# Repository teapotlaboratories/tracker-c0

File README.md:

# Tracker C0: Low-power Cellular GPS Tracker

Tracker C0 is a small, low-cost tracker board from Teapot Laboratories. It reports its position over LTE Cat-1 and is
meant to run for **at least a year on one battery**. To get there it spends almost all of its time in deep sleep,
wakes up when the accelerometer feels movement, takes a GNSS fix, sends a report over the cellular network, and goes
back to sleep with the modem and GNSS fully powered off.

> Formerly BWLC1A; the old GitHub URL redirects here.

| | |
|---|---|
| **Revision** | Rev 5 in progress on `main` (adds fiducials). Rev 4 (tag `rev4`) is ordered and not yet built or measured. |
| **Controller** | Espressif ESP32-S3-MINI-1-N4R2 (U4): Wi-Fi, Bluetooth LE, USB, deep sleep with RTC wake |
| **Cellular** | SIMCom A7670G-LABE (U1), LTE Cat-1, nano-SIM (J1) |
| **GNSS** | Quectel L96-M33 (U3), GPS / GLONASS / Galileo / BeiDou, built-in antenna, battery-backed hot starts |
| **Motion wake** | ST LSM6DSO 6-axis IMU (U11), INT1 to an RTC-capable ESP32 pin |
| **Battery** | Single-cell LiPo on a JST-PH 2-pin connector (J4), MAX17048 fuel gauge (U10) |
| **Charging** | USB-C (J3), MCP73831 linear charger (U8), 500 mA |
| **LTE antenna** | TE 2108784-1 PCB antenna (E1), or a u.FL connector (J6/J7) selected by resistors |
| **Expansion** | Qwiic / STEMMA QT I²C connector (J5), Tag-Connect TC2050 JTAG pads (J2), reset and boot buttons (SW1, SW2) |
| **Board** | 83.75 × 50.0 mm, 4 layers, 1.6 mm, 50 Ω coplanar antenna feed, all parts on the top side |

## Gallery

| Top | Bottom |
|---|---|
|  |  |
|  |  |

## Architecture

```mermaid
flowchart LR
    USB["USB-C<br/>J3"] -->|VBUS| CHG["MCP73831<br/>charger U8"]
    USB -->|"USB D+/D−"| MCU
    CHG --> BATT(("+BATT"))
    CELL["LiPo cell<br/>J4"] -->|"Q3 reverse<br/>protection"| BATT

    BATT --> LDO["RT9080 3.3 V<br/>always on"]
    LDO -->|+3V3| MCU["ESP32-S3<br/>U4"]
    LDO -->|+3V3| IMU["LSM6DSO<br/>IMU"]
    BATT --> FG["MAX17048<br/>fuel gauge"]
    BATT -->|"Q7 switch<br/>CELL_EN"| MODEM["A7670G<br/>LTE modem"]
    BATT -->|"TPS7A03 LDO<br/>GNSS_EN"| GNSS["L96-M33<br/>GNSS"]
    BATT -->|V_BCKP| GNSS

    IMU -->|"INT1 → GPIO14<br/>(wake)"| MCU
    FG -->|"ALERT → GPIO18"| MCU
    MCU <-->|"I²C (+ Qwiic J5)"| IMU
    MCU <-->|I²C| FG
    MCU <-->|"UART 3.3 V"| SHIFT["TXB0102<br/>level shifter"]
    SHIFT <-->|"UART 1.8 V"| MODEM
    MCU -->|"PWRKEY / RESET<br/>open-drain FETs"| MODEM
    MODEM -->|"STATUS → inverter"| MCU
    MCU <-->|UART| GNSS
    MODEM --- SIM["nano-SIM"]
    MODEM --- ANT["LTE antenna E1<br/>or u.FL J6/J7"]
```

### Power

Everything runs from the single-cell battery rail **+BATT**. While the tracker sleeps, only the 3.3 V regulator and
what it feeds (ESP32, IMU, the idle TXB0102 B side), the fuel gauge and the GNSS backup domain are powered.

| Rail | Source | Feeds | Switched by |
|---|---|---|---|
| +BATT | LiPo through Q3 (PMV32UP, reverse protection); charged by U8 from USB | everything below | always on |
| +3V3 | U6 RT9080-33 LDO | ESP32-S3, LSM6DSO, TXB0102 B side, Qwiic J5 | always on |
| CELL_BATT | +BATT through Q7 (PMV32UP P-FET), driven by Q8 (2N7002) | A7670G VBAT (soft start ~15 ms) | CELL_EN, GPIO13 |
| GNSS_3V3 | U7 TPS7A0333 LDO | L96-M33 VCC | GNSS_EN, GPIO4 |
| V_BCKP | +BATT directly | L96-M33 backup (keeps ephemeris for hot starts) | always on |
| VDD_1V8 | A7670G output | TXB0102 A side | on while the modem is on |

The modem draws up to about 2 A in bursts, so it takes its supply straight from the battery through a P-FET switch
rather than through a regulator.

### Operating cycle

```mermaid
stateDiagram-v2
    [*] --> DeepSleep
    DeepSleep --> Fix: IMU motion interrupt (GPIO14)<br/>or RTC timer
    Fix --> Report: GNSS_EN high, wait for a fix<br/>(hot start from V_BCKP)
    Report --> Shutdown: CELL_EN high, PWRKEY pulse,<br/>STATUS low = modem up, send report
    Shutdown --> DeepSleep: AT+CPOF, then CELL_EN low<br/>GNSS_EN low
```

### Estimated sleep budget

Datasheet typical values, **not measured yet**. Details and sources are in the
[Rev 4 change report](docs/worklog/2026-11-19-rev4-changes.html).

| In deep sleep | Current |
|---|---|
| ESP32-S3, RTC on for wake | 8 µA |
| LSM6DSO, low-power wake-up mode | 4.4 to 9.5 µA |
| L96-M33 backup domain | 7 µA |
| MAX17048, hibernate | 3 to 5 µA |
| RT9080 quiescent | 2 µA |
| TXB0102, charger, switched-off regulators, ESD | ≤ 4 µA |
| **Total** | **about 27 to 40 µA, about 240 to 350 mAh per year** |

With an assumed 1.5 mAh per wake-up (about 20 s GNSS fix plus 30 s LTE report), four wake-ups a day fit a 3 to 4 Ah
LiPo for one year. Measure sleep and event current on the first boards before choosing the cell.

## ESP32-S3 pin map

| GPIO | Net | Use |
|---|---|---|
| GPIO0 | BOOT_MODE0 | Boot strap, BOOT button SW2 |
| GPIO1 | GNSS_RESET | L96 reset, **drive open-drain only** (no pull-up) |
| GPIO4 | GNSS_EN | GNSS LDO enable |
| GPIO5 | GNSS_FO | L96 force-on |
| GPIO6 | GNSS_EXTINT | L96 external interrupt |
| GPIO7 / GPIO8 | GNSS_RXD / GNSS_TXD | GNSS UART |
| GPIO9 | CELL_PWRKEY | Modem PWRKEY through Q4, active high |
| GPIO10 / GPIO11 | CELL_TXD / CELL_RXD | Modem UART through the TXB0102 |
| GPIO12 | CELL_RESET | Modem RESET through Q5, active high |
| GPIO13 | CELL_EN | Modem battery switch Q7 |
| GPIO14 | IMU_INT | LSM6DSO INT1, deep-sleep wake source |
| GPIO17 | CELL_STATUS_N | Modem STATUS through the Q6 inverter, **low = modem on** |
| GPIO18 | FG_INT | MAX17048 ALERT |
| GPIO19 / GPIO20 | USB_D− / USB_D+ | Native USB on the USB-C connector |
| GPIO21 | GNSS_STAT | L96 status |
| GPIO36 / GPIO37 | SCL / SDA | I²C: IMU, fuel gauge, Qwiic J5 |
| GPIO39 to GPIO42 | JTAG_TCK / TDO / TDI / TMS | Tag-Connect J2 |
| GPIO47 / GPIO48 | LEDs | D6 / D5 |
| EN | CHIP_EN | Reset button SW1, Tag-Connect J2 |

### Firmware notes

- PWRKEY and RESET are pulled up to VBAT inside the modem. They are driven only through the Q4 and Q5 open-drain
  N-FETs, which are active high. Never assert both at the same time (A7670 hardware design guide).
- Before switching the modem off with CELL_EN, send `AT+CPOF`. Wait at least 5 s before switching it on again.
- GNSS_RESET has no pull-up: drive GPIO1 open-drain only.
- The modem UART is 1.8 V on the modem side. The TXB0102 translates it and goes high-impedance while the modem's
  1.8 V rail is off, so nothing back-powers the modem.

## Schematic

The KiCad 10 project is in [`hardware/kicad/`](hardware/kicad): the root sheet `tracker-c0.kicad_sch` plus eight
sub-sheets (Power, Battery, USB and Charger, Main Controller, Cellular, GNSS, Sensors, Antenna), the board
`tracker-c0.kicad_pcb`, and project libraries in `library/`.

## Manufacturing

Production files are in [`hardware/kicad/production/`](hardware/kicad/production):

| File | Contents |
|---|---|
| `TeapotlabsTrackerC0_Gerber.zip` | Gerbers, PTH/NPTH drill, IPC-D-356 netlist, PCBWay BOM and positions |
| `TeapotlabsTrackerC0_BOM.csv` | Bill of materials: 53 lines, 112 parts, with LCSC, Mouser or Digi-Key part numbers |
| `TeapotlabsTrackerC0_CPL.csv` | Pick-and-place positions (top side only) |
| `TeapotlabsTrackerC0_ManufacturingInfo.txt` | Board spec, stack-up and impedance notes for the fab |
| `TeapotlabsTrackerC0_InteractiveBOM.html` | Interactive BOM for hand assembly and inspection (open in a browser) |

Board spec: 4 layers, 1.6 mm, S1000H TG150, 5/5 mil, 0.3 mm minimum hole, tented vias, red solder mask with white
silkscreen. The LTE antenna feed is a 50 Ω coplanar waveguide on L1 (0.33 mm trace, 0.2 mm gap, referenced to L2),
so order with impedance control. Copper stays 0.3 mm from the board edge. Use a 0.12 mm stencil: U1 (A7670G) carries
SIMCom's recommended stencil openings, which need 0.12 to 0.15 mm.

Rebuild and check the production files with KiCad 10 installed:

```
hardware/tools/fab/export_production.sh          # BOM, CPL, Gerber zip, interactive BOM
python3 hardware/tools/fab/check_production.py   # board, BOM, CPL and PCBWay files must agree (PASS/FAIL)
```

The production check for PCBWay (BOM and CPL verification, board-edge and stencil fixes, part swaps) is in
[`docs/worklog/2026-11-19-pcbway-readiness.html`](docs/worklog/2026-11-19-pcbway-readiness.html).

## What changed in Rev 5 (in progress)

- **Fiducials:** three global fiducials on the top side (FID1-FID3: 1 mm copper in a 2 mm mask opening) for
  pick-and-place alignment. They are board-only, so the BOM and CPL are unchanged.
- **Board colour:** the stack-up mask colour is set to red, so KiCad's 3D view matches the boards as ordered.

The Rev 4 files as ordered from PCBWay are tagged `rev4`.

## What changed in Rev 4

- **Modem UART translator:** the 4-channel TXB0104 became a 2-channel TXB0102. Modem RESET now has its own open-drain
  driver (Q5) on GPIO12.
- **Modem STATUS:** the 1.8 V STATUS output is read through a FET inverter (Q6), so GPIO17 sees a clean 3.3 V level.
- **Modem power:** the SY8089 buck is gone. The modem runs straight from the battery through a P-FET switch with a
  soft start.
- **GNSS:** the reset pull-up that back-fed current in sleep is removed. The GNSS backup supply is wired straight to
  the battery, so every fix is a hot start; the backup switch and jumper are gone.
- **Assembly:** the battery connector moved to the top, so the board is single-sided. The corner is cut away for the
  battery cable.
- **Schematic readability** and a refreshed set of production files.

The full report with before/after schematic, PCB and 3D views is
[`docs/worklog/2026-11-19-rev4-changes.html`](docs/worklog/2026-11-19-rev4-changes.html). Download or clone the
repository and open it in a browser; GitHub shows HTML files as source.

## Repository layout

```
hardware/
  kicad/          KiCad 10 project, libraries, 3D models
    production/   Gerbers, BOM, CPL, manufacturing notes, interactive BOM
  tools/fab/      Production export and pre-order check
  tools/ibom/     Interactive BOM generator
docs/
  images/         README images and report images (Git LFS)
  worklog/        Design change reports
```

Images under `docs/images/` and the 3D models are stored with [Git LFS](https://git-lfs.com). Install it before
cloning to get the files instead of pointer stubs.

## License

[MIT](LICENSE)

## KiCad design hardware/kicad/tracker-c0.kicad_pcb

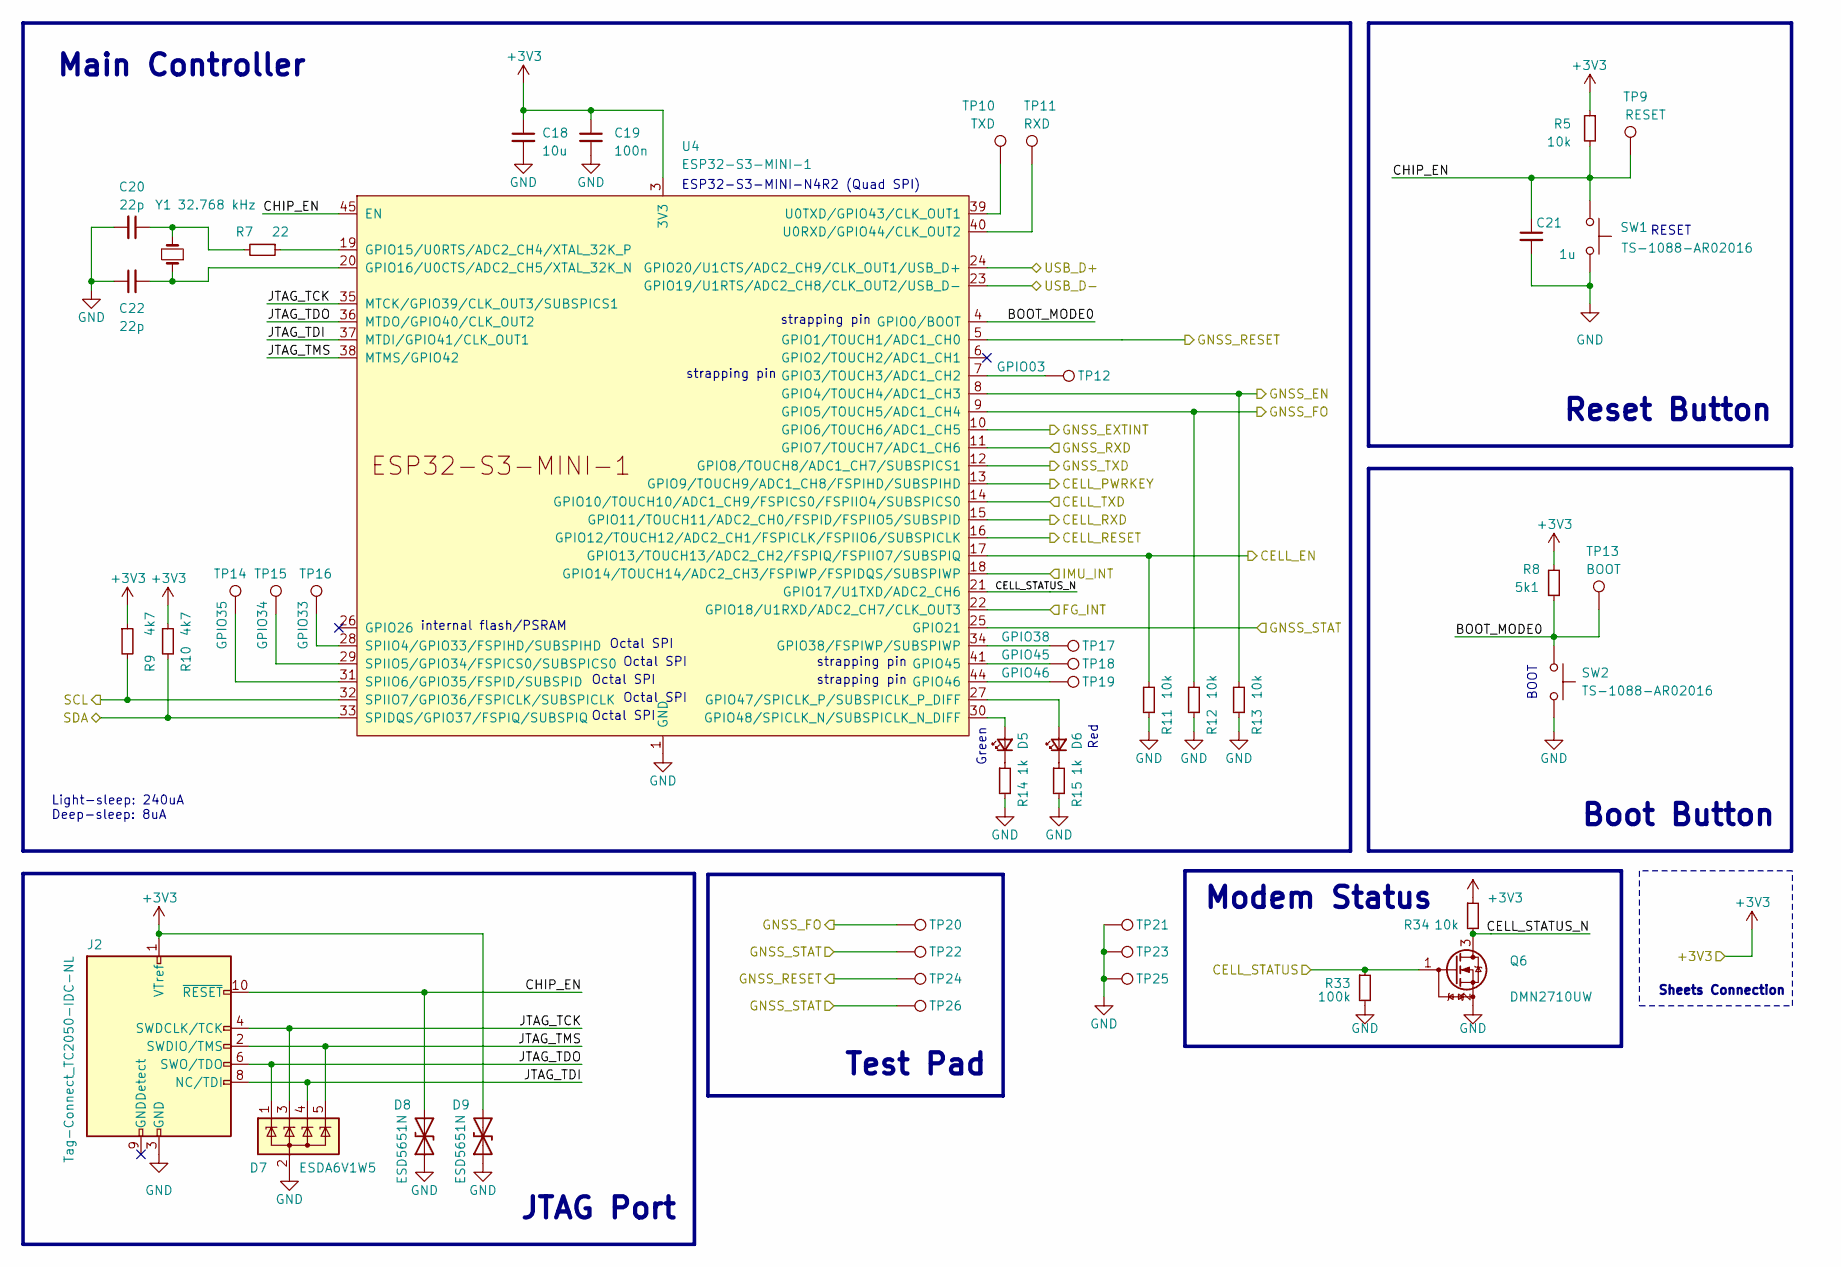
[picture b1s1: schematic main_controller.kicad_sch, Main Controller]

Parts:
C18: 10u; C_0603_1608Metric; Manufacturer Part Number CL10A106KP8NNNC
C19: 100n; C_0402_1005Metric; Manufacturer Part Number CL05B104KO5NNNC
C20, C22: 22p; C_0402_1005Metric; Manufacturer Part Number 0402CG220J500NT
C21: 1u; C_0402_1005Metric; Manufacturer Part Number CL05A105KA5NQNC
D5: LTST-C191KGKT; LED_0603_1608Metric; Manufacturer Part Number LTST-C191KGKT
D6: LTST-C191KRKT; LED_0603_1608Metric; Manufacturer Part Number LTST-C191KRKT
D7: ESDA6V1W5; SOT-353_SC-70-5; Manufacturer Part Number ESDA6V1W5
D8, D9: ESD5651N; D_SOD-882; Manufacturer Part Number ESD5651N
J2: Tag-Connect_TC2050-IDC-NL; Tag-Connect_TC2050-IDC-NL_2x05_P1.27mm_Vertical
Q6: DMN2710UW; SOT-323_SC-70; Manufacturer Part Number DMN2710UW-7
R5, R11, R12, R13, R34: 10k; R_0402_1005Metric; Manufacturer Part Number FRC0402F1002TS
R7: 22; R_0402_1005Metric; Manufacturer Part Number RC0402FR-0722RL
R8: 5k1; R_0402_1005Metric; Manufacturer Part Number 0402WGF5101TCE
R9, R10: 4k7; R_0402_1005Metric; Manufacturer Part Number 0402WGF4701TCE
R14, R15: 1k; R_0402_1005Metric; Manufacturer Part Number 0402WGF1001TCE
R33: 100k; R_0402_1005Metric; Manufacturer Part Number 0402WGF1003TCE
SW1, SW2: TS-1088-AR02016; SW-SMD_L3.9-W3.0-P4.45; Manufacturer Part Number TS-1088-AR02016
TP9: RESET; TestPoint_Pad_D1.0mm
TP10: TXD; TestPoint_Pad_D1.0mm
TP11: RXD; TestPoint_Pad_D1.0mm
TP12: GPIO03; TestPoint_Pad_D1.0mm
TP13: BOOT; TestPoint_Pad_D1.0mm
TP14: GPIO35; TestPoint_Pad_D1.0mm
TP15: GPIO34; TestPoint_Pad_D1.0mm
TP16: GPIO33; TestPoint_Pad_D1.0mm
TP17: GPIO38; TestPoint_Pad_D1.0mm
TP18: GPIO45; TestPoint_Pad_D1.0mm
TP19: GPIO46; TestPoint_Pad_D1.0mm
TP20, TP21, TP22, TP23, TP24, TP25, TP26: TestPoint_Pad_D1.0mm
U4: ESP32-S3-MINI-1; Manufacturer Part Number ESP32-S3-MINI-1-N4R2
Y1: 32.768 kHz; Crystal_SMD_3215-2Pin_3.2x1.5mm; Manufacturer Part Number Q13FC1350000400

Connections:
+3V3: C18.1, C19.1, D9.2 (A2), J2.1 (VTref), R5.1, R8.2, R9.1, R10.1, R34.1, U4.3 (3V3); also elsewhere on the board
/Cellular/CELL_PWRKEY: U4.13 (GPIO9/TOUCH9/ADC1_CH8/FSPIHD/SUBSPIHD); also elsewhere on the board
/Cellular/CELL_RESET: U4.16 (GPIO12/TOUCH12/ADC2_CH1/FSPICLK/FSPIIO6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); also elsewhere on the board
/Cellular/CELL_RXD: U4.15 (GPIO11/TOUCH11/ADC2_CH0/FSPID/FSPIIO5/S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); also elsewhere on the board
/Cellular/CELL_STATUS: Q6.1 (G), R33.1; also elsewhere on the board
/Cellular/CELL_TXD: U4.14 (GPIO10/TOUCH10/ADC1_CH9/FSPICS0/FSPIIO4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); also elsewhere on the board
/GNSS/GNSS_EXTINT: U4.10 (GPIO6/TOUCH6/ADC1_CH5); also elsewhere on the board
/GNSS/GNSS_FO: R12.2, TP20.1, U4.9 (GPIO5/TOUCH5/ADC1_CH4); also elsewhere on the board
/GNSS/GNSS_RESET: TP24.1, U4.5 (GPIO1/TOUCH1/ADC1_CH0); also elsewhere on the board
/GNSS/GNSS_RXD: U4.11 (GPIO7/TOUCH7/ADC1_CH6); also elsewhere on the board
/GNSS/GNSS_STAT: TP22.1, TP26.1, U4.25 (GPIO21); also elsewhere on the board
/GNSS/GNSS_TXD: U4.12 (GPIO8/TOUCH8/ADC1_CH7/SUBSPICS1); also elsewhere on the board
/Main Controller/BOOT_MODE0: R8.1, SW2.1, TP13.1, U4.4 (GPIO0/BOOT)
/Main Controller/CELL_EN: R11.2, U4.17 (GPIO13/TOUCH13/ADC2_CH2/FSPIQ/FSPIIO7/S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); also elsewhere on the board
/Main Controller/CELL_STATUS_N: Q6.3 (D), R34.2, U4.21 (GPIO17/U1TXD/ADC2_CH6)
/Main Controller/CHIP_EN: C21.1, D8.2 (A2), J2.10 (~RESET), R5.2, SW1.2, TP9.1, U4.45 (EN)
/Main Controller/FG_INT: U4.22 (GPIO18/U1RXD/ADC2_CH7/CLK_OUT3); also elsewhere on the board
/Main Controller/GNSS_EN: R13.2, U4.8 (GPIO4/TOUCH4/ADC1_CH3); also elsewhere on the board
/Main Controller/IMU_INT: U4.18 (GPIO14/TOUCH14/ADC2_CH3/FSPIWP/FSPIDQS/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); also elsewhere on the board
/Main Controller/JTAG_TCK: D7.3 (K), J2.4 (SWDCLK/TCK), U4.35 (MTCK/GPIO39/CLK_OUT3/SUBSPICS1)
/Main Controller/JTAG_TDI: D7.4 (K), J2.8 (NC/TDI), U4.37 (MTDI/GPIO41/CLK_OUT1)
/Main Controller/JTAG_TDO: D7.1 (K), J2.6 (SWO/TDO), U4.36 (MTDO/GPIO40/CLK_OUT2)
/Main Controller/JTAG_TMS: D7.5 (K), J2.2 (SWDIO/TMS), U4.38 (MTMS/GPIO42)
/Main Controller/SCL: R9.2, U4.32 (SPIIO7/GPIO36/FSPICLK/SUBSPICLK); also elsewhere on the board
/Main Controller/SDA: R10.2, U4.33 (SPIDQS/GPIO37/FSPIQ/SUBSPIQ); also elsewhere on the board
/Main Controller/USB_D+: U4.24 (GPIO20/U1CTS/ADC2_CH9/CLK_OUT1/USB_D+); also elsewhere on the board
/Main Controller/USB_D-: U4.23 (GPIO19/U1RTS/ADC2_CH8/CLK_OUT2/USB_D-); also elsewhere on the board
GND: C18.2, C19.2, C20.2, C21.2, C22.1, D7.2 (A), D8.1 (A1), D9.1 (A1), J2.3 (GND), J2.5 (GND), Q6.2 (S), R11.1, R12.1, R13.1, R14.2, R15.2, R33.2, SW1.1, SW2.2, TP21.1, TP23.1, TP25.1, U4.1 (GND), U4.2 (GND), U4.42 (GND), U4.43 (GND), U4.46 (GND), U4.47 (GND), U4.48 (GND), U4.49 (GND), U4.50 (GND), U4.51 (GND), U4.52 (GND), U4.53 (GND), U4.54 (GND), U4.55 (GND), U4.56 (GND), U4.57 (GND), U4.58 (GND), U4.59 (GND), U4.60 (GND), U4.61 (GND), U4.62 (GND), U4.63 (GND), U4.64 (GND), U4.65 (GND); also elsewhere on the board
unnamed: C20.1, R7.2, Y1.2
unnamed: D5.2 (A), U4.30 (GPIO48/SPICLK_N/SUBSPICLK_N_DIFF)
unnamed: D5.1 (K), R14.1
unnamed: D6.2 (A), U4.27 (GPIO47/SPICLK_P/SUBSPICLK_P_DIFF)
unnamed: D6.1 (K), R15.1
unnamed: TP12.1, U4.7 (GPIO3/TOUCH3/ADC1_CH2)
unnamed: R7.1, U4.19 (GPIO15/U0RTS/ADC2_CH4/XTAL_32K_P)
unnamed: C22.2, U4.20 (GPIO16/U0CTS/ADC2_CH5/XTAL_32K_N), Y1.1
unnamed: TP17.1, U4.34 (GPIO38/FSPIWP/SUBSPIWP)
unnamed: TP18.1, U4.41 (GPIO45)
unnamed: TP19.1, U4.44 (GPIO46)
unnamed: TP16.1, U4.28 (SPIIO4/GPIO33/FSPIHD/SUBSPIHD)
unnamed: TP15.1, U4.29 (SPIIO5/GPIO34/FSPICS0/SUBSPICS0)
unnamed: TP14.1, U4.31 (SPIIO6/GPIO35/FSPID/SUBSPID)
unnamed: TP11.1, U4.40 (U0RXD/GPIO44/CLK_OUT2)
unnamed: TP10.1, U4.39 (U0TXD/GPIO43/CLK_OUT1)

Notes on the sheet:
ESP32-S3-MINI-N4R2 (Quad SPI)
Red
Test Pad
Reset Button
strapping pin
Octal SPI
Main Controller
JTAG Port
Green
Boot Button
RESET
Sheets Connection
internal flash/PSRAM
BOOT
Light-sleep: 240uA Deep-sleep: 8uA
Modem Status

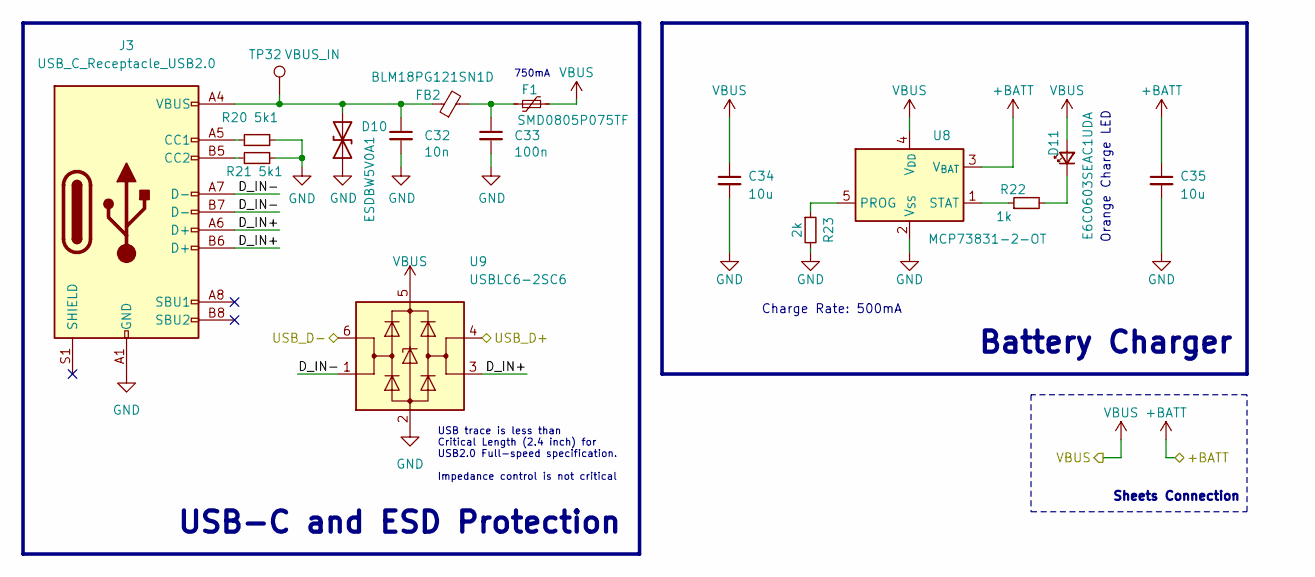
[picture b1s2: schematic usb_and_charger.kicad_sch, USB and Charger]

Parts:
C32: 10n; C_0402_1005Metric; Manufacturer Part Number CL05B103KB5NNNC
C33: 100n; C_0402_1005Metric; Manufacturer Part Number CL05B104KO5NNNC
C34, C35: 10u; C_0603_1608Metric; Manufacturer Part Number CL10A106KP8NNNC
D10: ESDBW5V0A1; D_SOD-882; Manufacturer Part Number ESDBW5V0A1
D11: E6C0603SEAC1UDA; LED_0603_1608Metric; Manufacturer Part Number E6C0603SEAC1UDA
F1: SMD0805P075TF; Fuse_0805_2012Metric; Manufacturer Part Number SMD0805P075TF
FB2: BLM18PG121SN1D; L_0603_1608Metric; Manufacturer Part Number BLM18PG121SN1D
J3: USB_C_Receptacle_USB2.0; USB_C_Receptacle_HRO_TYPE-C-31-M-12; Manufacturer Part Number TYPE-C-31-M-12
R20, R21: 5k1; R_0402_1005Metric; Manufacturer Part Number 0402WGF5101TCE
R22: 1k; R_0402_1005Metric; Manufacturer Part Number 0402WGF1001TCE
R23: 2k; R_0402_1005Metric; Manufacturer Part Number 0402WGF2001TCE
TP32: VBUS_IN; TestPoint_Pad_D1.0mm
U8: MCP73831-2-OT; SOT-23-5; Manufacturer Part Number MCP73831T-2ATI/OT
U9: USBLC6-2SC6; SOT-23-6; Manufacturer Part Number USBLC6-2SC6

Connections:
+BATT: C35.1, U8.3 (V_{BAT}); also elsewhere on the board
/Main Controller/USB_D+: U9.4 (I/O2); also elsewhere on the board
/Main Controller/USB_D-: U9.6 (I/O1); also elsewhere on the board
/USB and Charger/D_IN+: J3.A6 (D+), J3.B6 (D+), U9.3 (I/O2)
/USB and Charger/D_IN-: J3.A7 (D-), J3.B7 (D-), U9.1 (I/O1)
GND: C32.2, C33.2, C34.2, C35.2, D10.1 (A1), J3.A1 (GND), J3.A12 (GND), J3.B1 (GND), J3.B12 (GND), R20.2, R21.2, R23.2, U8.2 (V_{SS}), U9.2 (GND); also elsewhere on the board
unnamed: C33.1, F1.1, FB2.2
unnamed: C32.1, D10.2 (A2), FB2.1, J3.A4 (VBUS), J3.A9 (VBUS), J3.B4 (VBUS), J3.B9 (VBUS), TP32.1
unnamed: D11.1 (K), R22.2
unnamed: J3.A5 (CC1), R20.1
unnamed: J3.B5 (CC2), R21.1
unnamed: R23.1, U8.5 (PROG)
unnamed: R22.1, U8.1 (STAT)
VBUS: C34.1, D11.2 (A), F1.2, U8.4 (V_{DD}), U9.5 (VBUS)

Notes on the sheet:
Orange Charge LED
Battery Charger
USB trace is less than Critical Length (2.4 inch) for USB2.0 Full-speed specification. Impedance control is not critical
Sheets Connection
750mA
Charge Rate: 500mA
USB-C and ESD Protection

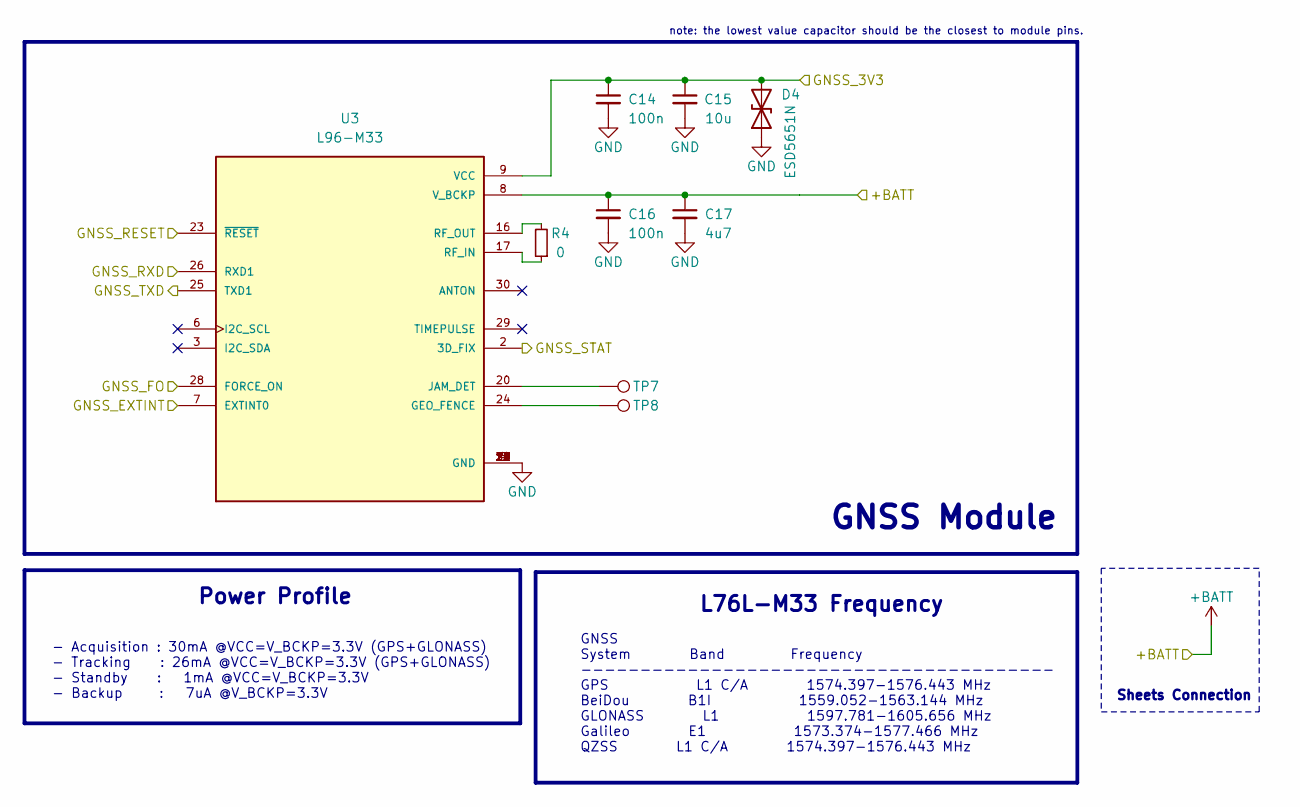
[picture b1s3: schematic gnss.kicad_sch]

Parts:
C14, C16: 100n; C_0402_1005Metric; Manufacturer Part Number CL05B104KO5NNNC
C15: 10u; C_0603_1608Metric; Manufacturer Part Number CL10A106KP8NNNC
C17: 4u7; C_0603_1608Metric; Manufacturer Part Number CL10A475KO8NNNC
D4: ESD5651N; D_SOD-882; Manufacturer Part Number ESD5651N
R4: 0; R_0402_1005Metric; Manufacturer Part Number 0402WGF0000TCE
TP7, TP8: GPIO46; TestPoint_Pad_D1.0mm
U3: L96-M33; Manufacturer Part Number L96-M33

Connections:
+BATT: C16.1, C17.1, U3.8 (V_BCKP); also elsewhere on the board
/GNSS/GNSS_EXTINT: U3.7 (EXTINT0); also elsewhere on the board
/GNSS/GNSS_FO: U3.28 (FORCE_ON); also elsewhere on the board
/GNSS/GNSS_RESET: U3.23 (~RESET); also elsewhere on the board
/GNSS/GNSS_RXD: U3.26 (RXD1); also elsewhere on the board
/GNSS/GNSS_STAT: U3.2 (3D_FIX); also elsewhere on the board
/GNSS/GNSS_TXD: U3.25 (TXD1); also elsewhere on the board
/GNSS_3V3: C14.1, C15.1, D4.2 (A2), U3.9 (VCC); also elsewhere on the board
GND: C14.2, C15.2, C16.2, C17.2, D4.1 (A1), U3.4 (GND), U3.5 (GND), U3.10 (GND), U3.11 (GND), U3.12 (GND), U3.13 (GND), U3.14 (GND), U3.15 (GND), U3.18 (GND), U3.19 (GND), U3.21 (GND), U3.22 (GND), U3.27 (GND), U3.31 (GND); also elsewhere on the board
unnamed: TP8.1, U3.24 (GEO_FENCE)
unnamed: TP7.1, U3.20 (JAM_DET)
unnamed: R4.1, U3.17 (RF_IN)
unnamed: R4.2, U3.16 (RF_OUT)

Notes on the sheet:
GNSS Module
- Acquisition : 30mA @VCC=V_BCKP=3.3V (GPS+GLONASS) - Tracking : 26mA @VCC=V_BCKP=3.3V (GPS+GLONASS) - Standby : 1mA @VCC=V_BCKP=3.3V - Backup : 7uA @V_BCKP=3.3V
Sheets Connection
L76L-M33 Frequency
note: the lowest value capacitor should be the closest to module pins.
GNSS System Band Frequency ---------------------------------------- GPS L1 C/A 1574.397-1576.443 MHz BeiDou B1I 1559.052-1563.144 MHz GLONASS L1 1597.781-1605.656 MHz Galileo E1 1573.374-1577.466 MHz QZSS L1 C/A 1574.397-1576.443 MHz
Power Profile

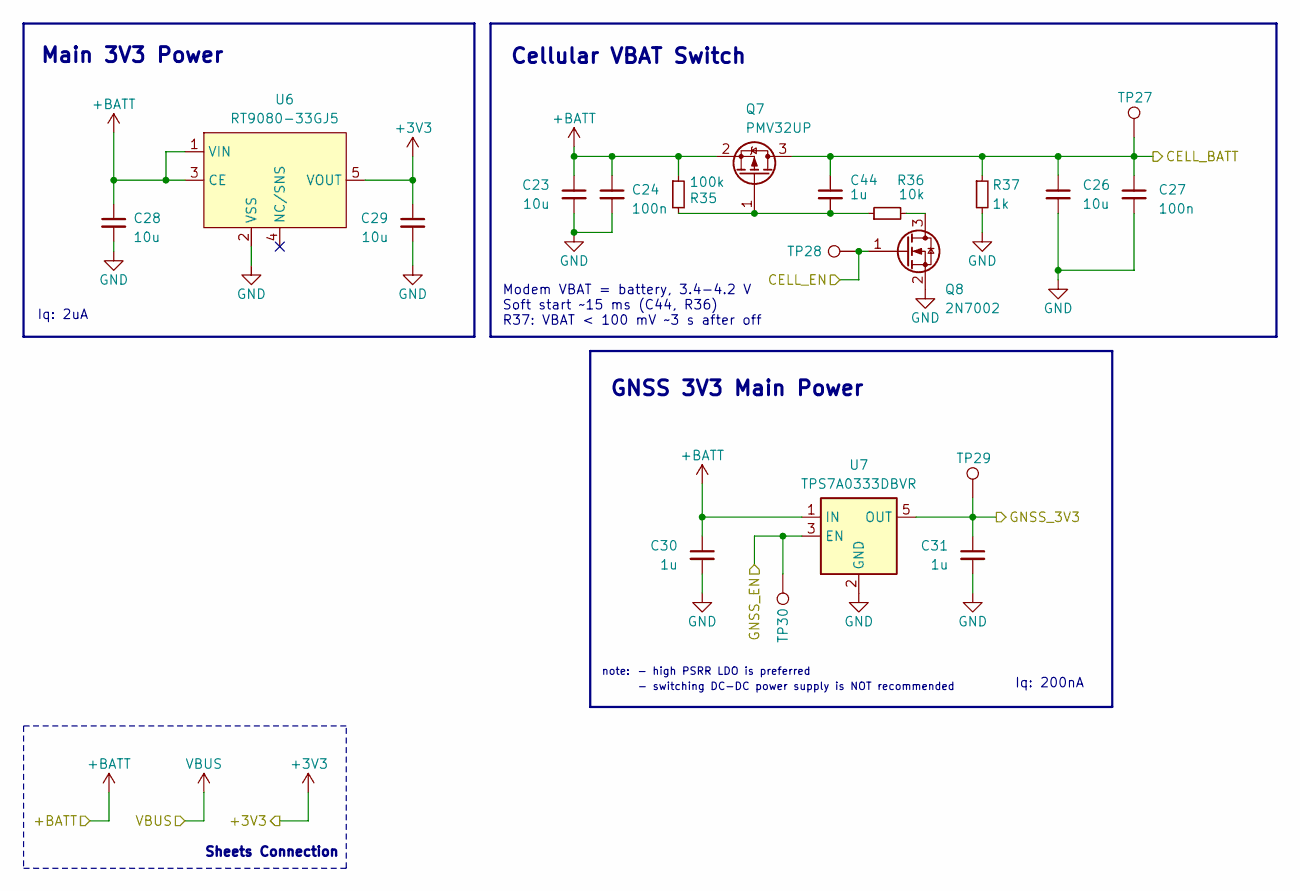
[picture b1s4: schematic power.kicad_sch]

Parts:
C23, C26, C28, C29: 10u; C_0603_1608Metric; Manufacturer Part Number CL10A106KP8NNNC
C24, C27: 100n; C_0603_1608Metric; Manufacturer Part Number CC0603KRX7R9BB104
C30, C31: 1u; C_0603_1608Metric; Manufacturer Part Number CL10B105KA8NNNC
C44: 1u; C_0402_1005Metric; Manufacturer Part Number CL05A105KA5NQNC
Q7: PMV32UP; SOT-23; Manufacturer Part Number PMV32UP
Q8: 2N7002; SOT-23; Manufacturer Part Number 2N7002
R35: 100k; R_0402_1005Metric; Manufacturer Part Number 0402WGF1003TCE
R36: 10k; R_0402_1005Metric; Manufacturer Part Number FRC0402F1002TS
R37: 1k; R_0402_1005Metric; Manufacturer Part Number 0402WGF1001TCE
TP27, TP28, TP29, TP30: TestPoint_Pad_D1.0mm
U6: RT9080-33GJ5; SOT-23-5; Manufacturer Part Number RT9080-33GJ5
U7: TPS7A0333DBVR; SOT-23-5; Manufacturer Part Number TPS7A0333DBVR

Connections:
+3V3: C29.1, U6.5 (VOUT); also elsewhere on the board
+BATT: C23.1, C24.1, C28.1, C30.1, Q7.2 (S), R35.1, U6.1 (VIN), U6.3 (CE), U7.1 (IN); also elsewhere on the board
/Cellular/CELL_BATT: C26.1, C27.1, C44.1, Q7.3 (D), R37.1, TP27.1; also elsewhere on the board
/GNSS_3V3: C31.1, TP29.1, U7.5 (OUT); also elsewhere on the board
/Main Controller/CELL_EN: Q8.1 (G), TP28.1; also elsewhere on the board
/Main Controller/GNSS_EN: TP30.1, U7.3 (EN); also elsewhere on the board
GND: C23.2, C24.2, C26.2, C27.2, C28.2, C29.2, C30.2, C31.2, Q8.2 (S), R37.2, U6.2 (VSS), U7.2 (GND); also elsewhere on the board
unnamed: C44.2, Q7.1 (G), R35.2, R36.1
unnamed: Q8.3 (D), R36.2

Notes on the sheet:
Cellular VBAT Switch
- switching DC-DC power supply is NOT recommended
- high PSRR LDO is preferred
Modem VBAT = battery, 3.4-4.2 V Soft start ~15 ms (C44, R36) R37: VBAT < 100 mV ~3 s after off
GNSS 3V3 Main Power
Iq: 2uA
Main 3V3 Power
Sheets Connection
note:
Iq: 200nA

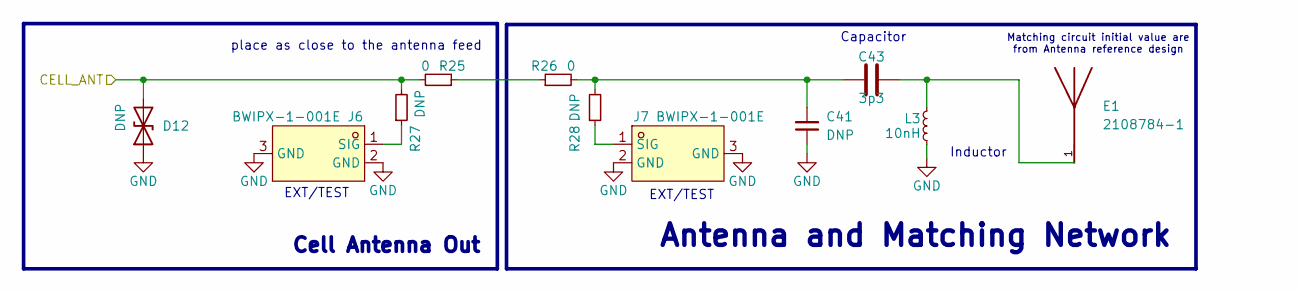
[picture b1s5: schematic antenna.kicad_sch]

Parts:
C41: DNP; C_0402_1005Metric
C43: 3p3; C_0402_1005Metric; Manufacturer Part Number GRM1555C1H3R3CA01D
D12: DNP; D_SOD-882
E1: 2108784-1; Manufacturer Part Number 2108784-1
J6, J7: BWIPX-1-001E; Manufacturer Part Number BWIPX-1-001E
L3: 10nH; L_0402_1005Metric; Manufacturer Part Number LQG15HS10NG02D
R25, R26: 0; R_0402_1005Metric; Manufacturer Part Number 0402WGF0000TCE
R27, R28: DNP; R_0402_1005Metric

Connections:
/Antenna/CELL_ANT: D12.2 (A2), R25.2, R27.2; also elsewhere on the board
GND: C41.1, D12.1 (A1), J6.2 (GND), J6.3 (GND), J7.2 (GND), J7.3 (GND), L3.1; also elsewhere on the board
unnamed: C41.2, C43.1, R26.2, R28.2
unnamed: C43.2, E1.1, L3.2
unnamed: J6.1 (SIG), R27.1
unnamed: J7.1 (SIG), R28.1
unnamed: R25.1, R26.1

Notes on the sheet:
Cell Antenna Out
EXT/TEST
Inductor
Antenna and Matching Network
Matching circuit initial value are from Antenna reference design
place as close to the antenna feed
Capacitor

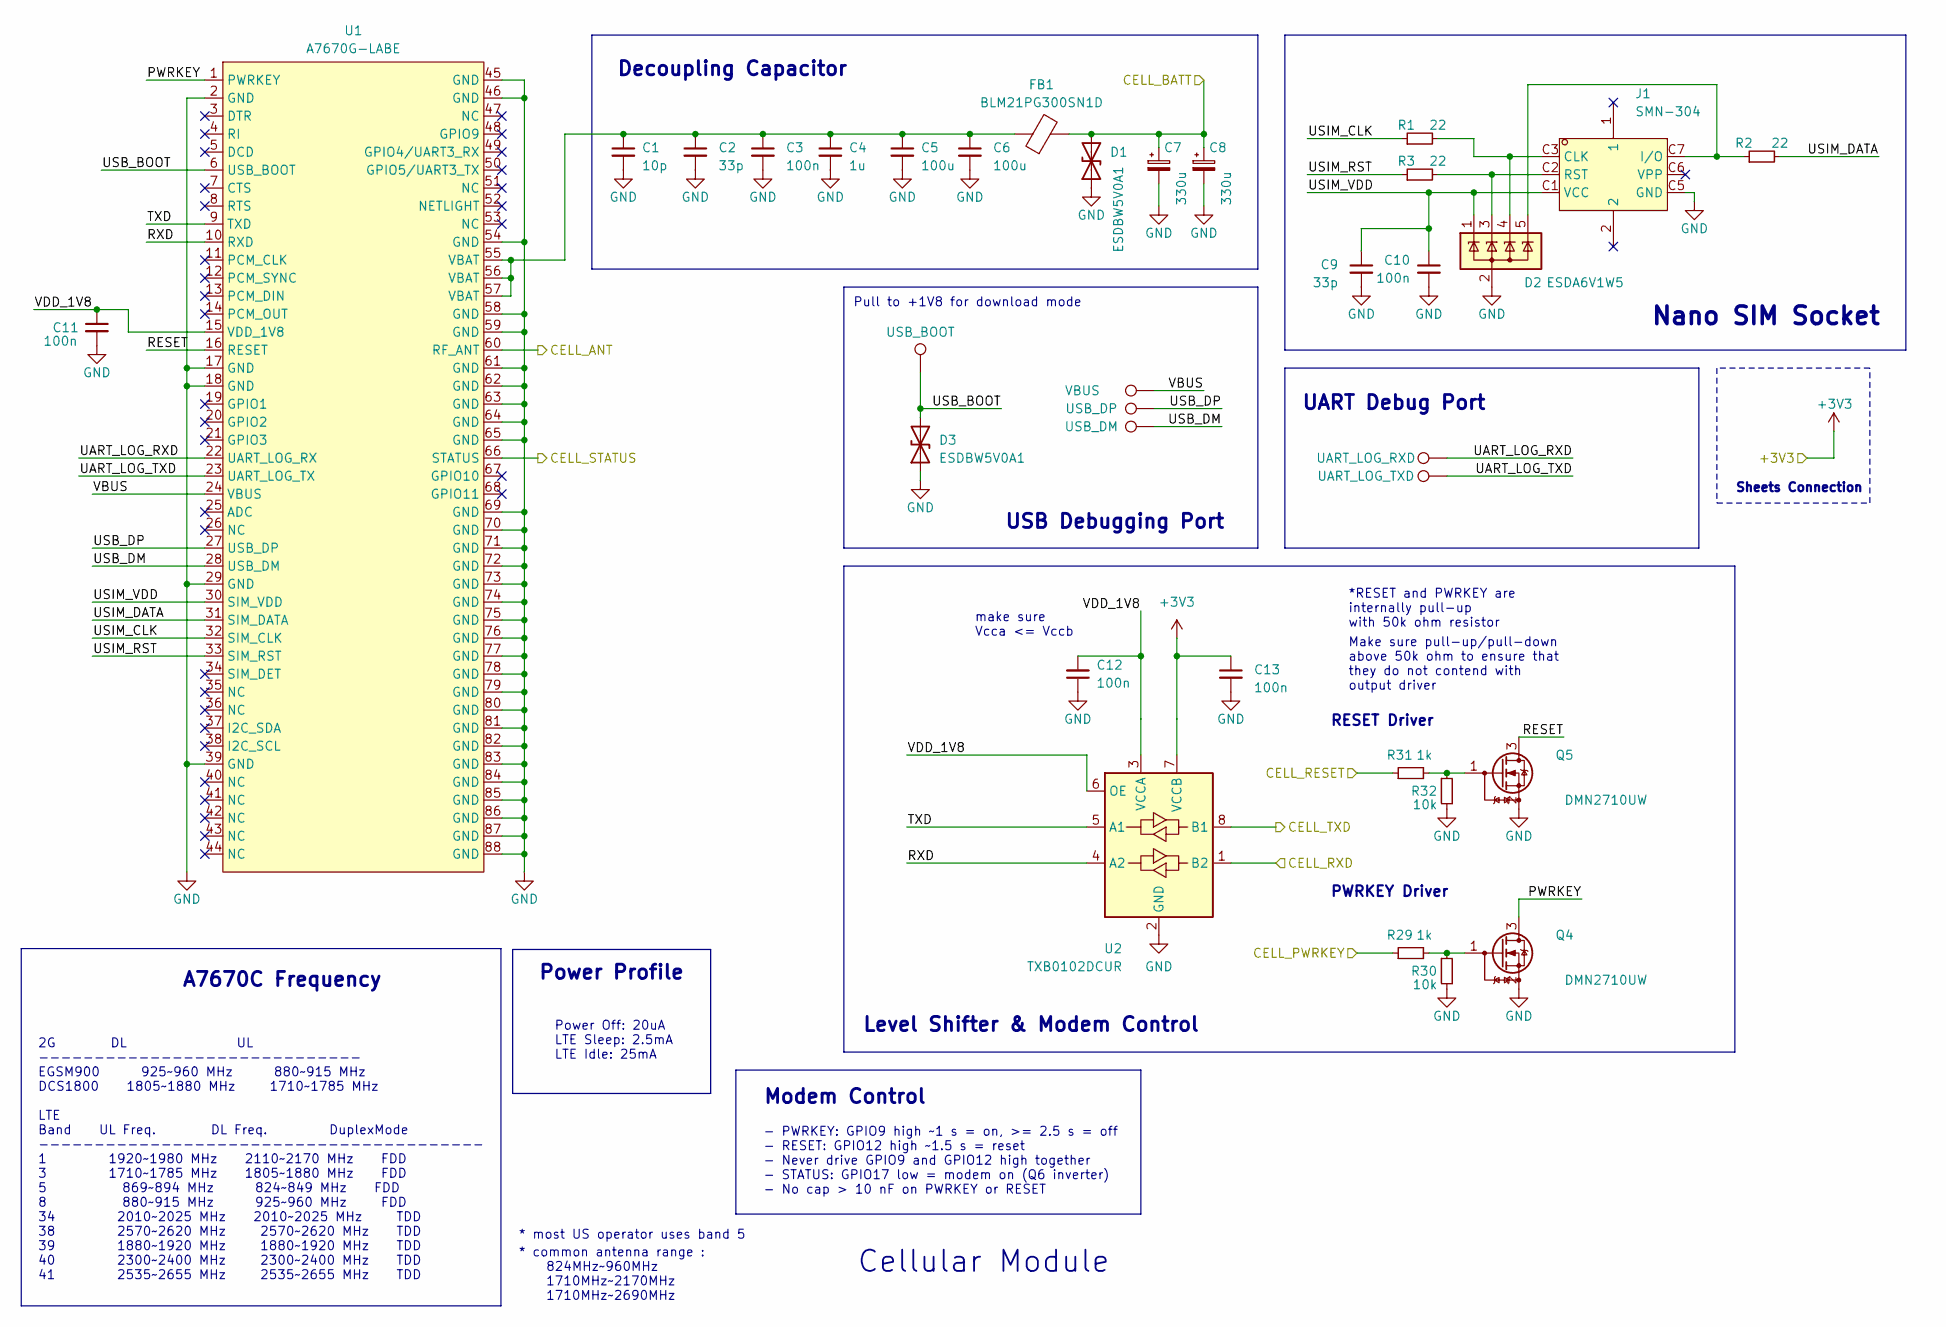
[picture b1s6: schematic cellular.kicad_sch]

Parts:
C1: 10p; C_0402_1005Metric; Manufacturer Part Number CL05C100JB5NNNC
C2, C9: 33p; C_0402_1005Metric; Manufacturer Part Number 0402CG330J500NT
C3, C10, C11, C12, C13: 100n; C_0402_1005Metric; Manufacturer Part Number CL05B104KO5NNNC
C4: 1u; C_0402_1005Metric; Manufacturer Part Number CL05A105KA5NQNC
C5, C6: 100u; C_0805_2012Metric; Manufacturer Part Number GRM21BR60J107ME15L
C7, C8: 330u; CP_EIA-3528-21_Kemet-B; Manufacturer Part Number T520B337M006ATE040
D1, D3: ESDBW5V0A1; D_SOD-882; Manufacturer Part Number ESDBW5V0A1
D2: ESDA6V1W5; SOT-353_SC-70-5; Manufacturer Part Number ESDA6V1W5
FB1: BLM21PG300SN1D; L_0805_2012Metric; Manufacturer Part Number BLM21PG300SN1D
J1: SMN-304; SIM-SMD_SMN-304; Manufacturer Part Number SMN-304
Q4, Q5: DMN2710UW; SOT-323_SC-70; Manufacturer Part Number DMN2710UW-7
R1, R2, R3: 22; R_0402_1005Metric; Manufacturer Part Number RC0402FR-0722RL
R29, R31: 1k; R_0402_1005Metric; Manufacturer Part Number 0402WGF1001TCE
R30, R32: 10k; R_0402_1005Metric; Manufacturer Part Number FRC0402F1002TS
TP1: USB_BOOT; TestPoint_Pad_D1.0mm
TP2: VBUS; TestPoint_Pad_D1.0mm
TP3: USB_DP; TestPoint_Pad_D1.0mm
TP4: USB_DM; TestPoint_Pad_D1.0mm
TP5: UART_LOG_RXD; TestPoint_Pad_D1.0mm
TP6: UART_LOG_TXD; TestPoint_Pad_D1.0mm
U1: A7670G-LABE; LGA-124_L24.0-W24.0-P1.0-A7670C-LASS; Manufacturer Part Number A7670G-LABE
U2: TXB0102DCUR; VSSOP-8_2.3x2mm_P0.5mm; Manufacturer Part Number TXB0102DCUR

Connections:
+3V3: C13.1, U2.7 (VCCB); also elsewhere on the board
/Antenna/CELL_ANT: U1.60 (RF_ANT); also elsewhere on the board
/Cellular/CELL_BATT: C7.1, C8.1, D1.2 (A2), FB1.2; also elsewhere on the board
/Cellular/CELL_PWRKEY: R29.1; also elsewhere on the board
/Cellular/CELL_RESET: R31.1; also elsewhere on the board
/Cellular/CELL_RXD: U2.1 (B2); also elsewhere on the board
/Cellular/CELL_STATUS: U1.66 (STATUS); also elsewhere on the board
/Cellular/CELL_TXD: U2.8 (B1); also elsewhere on the board
/Cellular/PWRKEY: Q4.3 (D), U1.1 (PWRKEY)
/Cellular/RESET: Q5.3 (D), U1.16 (RESET)
/Cellular/RXD: U1.10 (RXD), U2.4 (A2)
/Cellular/TXD: U1.9 (TXD), U2.5 (A1)
/Cellular/UART_LOG_RXD: TP5.1, U1.22 (UART_LOG_RX)
/Cellular/UART_LOG_TXD: TP6.1, U1.23 (UART_LOG_TX)
/Cellular/USB_BOOT: D3.2 (A2), TP1.1, U1.6 (USB_BOOT)
/Cellular/USB_DM: TP4.1, U1.28 (USB_DM)
/Cellular/USB_DP: TP3.1, U1.27 (USB_DP)
/Cellular/USIM_CLK: R1.1, U1.32 (SIM_CLK)
/Cellular/USIM_DATA: R2.2, U1.31 (SIM_DATA)
/Cellular/USIM_RST: R3.1, U1.33 (SIM_RST)
/Cellular/USIM_VDD: C9.1, C10.1, D2.1 (K), J1.C1 (VCC), U1.30 (SIM_VDD)
/Cellular/VBUS: TP2.1, U1.24 (VBUS)
/Cellular/VDD_1V8: C11.1, C12.2, U1.15 (VDD_1V8), U2.3 (VCCA), U2.6 (OE)
GND: C1.2, C2.2, C3.2, C4.2, C5.2, C6.2, C7.2, C8.2, C9.2, C10.2, C11.2, C12.1, C13.2, D1.1 (A1), D2.2 (A), D3.1 (A1), J1.C5 (GND), Q4.2 (S), Q5.2 (S), R30.2, R32.2, U1.2 (GND), U1.17 (GND), U1.18 (GND), U1.29 (GND), U1.39 (GND), U1.45 (GND), U1.46 (GND), U1.54 (GND), U1.58 (GND), U1.59 (GND), U1.61 (GND), U1.62 (GND), U1.63 (GND), U1.64 (GND), U1.65 (GND), U1.69 (GND), U1.70 (GND), U1.71 (GND), U1.72 (GND), U1.73 (GND), U1.74 (GND), U1.75 (GND), U1.76 (GND), U1.77 (GND), U1.78 (GND), U1.79 (GND), U1.80 (GND), U1.81 (GND), U1.82 (GND), U1.83 (GND), U1.84 (GND), U1.85 (GND), U1.86 (GND), U1.87 (GND), U1.88 (GND), U2.2 (GND); also elsewhere on the board
unnamed: C1.1, C2.1, C3.1, C4.1, C5.1, C6.1, FB1.1, U1.55 (VBAT), U1.56 (VBAT), U1.57 (VBAT)
unnamed: D2.4 (K), J1.C3 (CLK), R1.2
unnamed: D2.5 (K), J1.C7 (I/O), R2.1
unnamed: D2.3 (K), J1.C2 (RST), R3.2
unnamed: Q4.1 (G), R29.2, R30.1
unnamed: Q5.1 (G), R31.2, R32.1

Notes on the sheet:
Make sure pull-up/pull-down above 50k ohm to ensure that they do not contend with output driver
Decoupling Capacitor
Pull to +1V8 for download mode
Nano SIM Socket
make sure Vcca <= Vccb
*RESET and PWRKEY are internally pull-up with 50k ohm resistor
Power Off: 20uA LTE Sleep: 2.5mA LTE Idle: 25mA
Sheets Connection
A7670C Frequency
UART Debug Port
2G DL UL ----------------------------- EGSM900 925~960 MHz 880~915 MHz DCS1800 1805~1880 MHz 1710~1785 MHz LTE Band UL Freq. DL Freq. DuplexMode ---------------------------------------- 1 1920~1980 MHz 2110~2170 MHz FDD 3 1710~1785 MHz 1805~1880 MHz FDD 5 869~894 MHz 824~849 MHz FDD 8 880~915 MHz 9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
* most US operator uses band 5
USB Debugging Port
* common antenna range : 824MHz~960MHz 1710MHz~2170MHz 1710MHz~2690MHz
Power Profile
Cellular Module
RESET Driver
PWRKEY Driver
Level Shifter & Modem Control
Modem Control
- PWRKEY: GPIO9 high ~1 s = on, >= 2.5 s = off - RESET: GPIO12 high ~1.5 s = reset - Never drive GPIO9 and GPIO12 high together - STATUS: GPIO17 low = modem on (Q6 inverter) - No cap > 10 nF on PWRKEY or RESET
